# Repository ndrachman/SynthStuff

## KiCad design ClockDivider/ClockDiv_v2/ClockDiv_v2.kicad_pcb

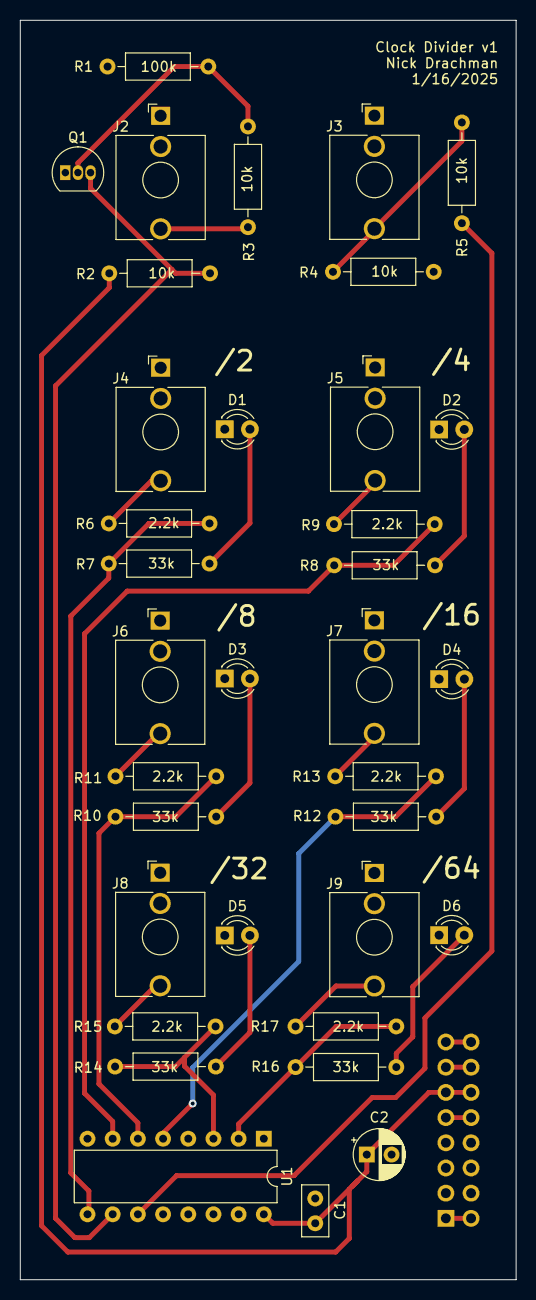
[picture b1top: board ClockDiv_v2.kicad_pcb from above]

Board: 2 copper layers, 50.0 x 127.0 mm, 36 parts (1 on the bottom side), 27 nets.

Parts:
C1: 0.1u; C_Disc_D5.0mm_W2.5mm_P2.50mm
C2: 10u; CP_Radial_D5.0mm_P2.50mm
D1, D2, D3, D4, D5, D6: LED; LED_D3.0mm
J2: ClockIn; Jack_3.5mm_QingPu_WQP-PJ398SM_Vertical_CircularHoles
J3: ResetIn; Jack_3.5mm_QingPu_WQP-PJ398SM_Vertical_CircularHoles
J4: /2; Jack_3.5mm_QingPu_WQP-PJ398SM_Vertical_CircularHoles
J5: /4; Jack_3.5mm_QingPu_WQP-PJ398SM_Vertical_CircularHoles
J6: /8; Jack_3.5mm_QingPu_WQP-PJ398SM_Vertical_CircularHoles
J7: /16; Jack_3.5mm_QingPu_WQP-PJ398SM_Vertical_CircularHoles
J8: /32; Jack_3.5mm_QingPu_WQP-PJ398SM_Vertical_CircularHoles
J9: /64; Jack_3.5mm_QingPu_WQP-PJ398SM_Vertical_CircularHoles
J10: Conn_02x08_Odd_Even; PinHeader_2x08_P2.54mm_Vertical
Q1: 2N3904; TO-92_Inline
R1: 100k; R_Axial_DIN0207_L6.3mm_D2.5mm_P10.16mm_Horizontal
R2, R3, R4, R5: 10k; R_Axial_DIN0207_L6.3mm_D2.5mm_P10.16mm_Horizontal
R6: 2.2k; R_Axial_DIN0207_L6.3mm_D2.5mm_P10.16mm_Horizontal
R7, R8, R10, R12, R14, R16: 33k; R_Axial_DIN0207_L6.3mm_D2.5mm_P10.16mm_Horizontal
R9, R11, R13, R15, R17: 2k2; R_Axial_DIN0207_L6.3mm_D2.5mm_P10.16mm_Horizontal
U1: 4040; DIP-16_W7.62mm

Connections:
+5V: C1.1, C2.1, J10.11, J10.12, R2.1, U1.16 (VDD)
+12V: J10.9, J10.10
-12V: J10.1, J10.2
GND: C1.2, C2.2, D1.1 (K), D2.1 (K), D3.1 (K), D4.1 (K), D5.1 (K), D6.1 (K), J2.S, J3.S, J4.S, J5.S, J6.S, J7.S, J8.S, J9.S, J10.3, J10.4, J10.5, J10.6, J10.7, J10.8, Q1.1 (E), R1.1, R4.2, U1.8 (VSS)
unnamed: D1.2 (A), R7.2
unnamed: D2.2 (A), R8.2
unnamed: D3.2 (A), R10.2
unnamed: D4.2 (A), R12.2
unnamed: D5.2 (A), R14.2
unnamed: D6.2 (A), R16.2
unnamed: J2.T, R3.2
unnamed: J3.T, R4.1, R5.2
unnamed: J4.T, R6.1
unnamed: J5.T, R9.1
unnamed: J6.T, R11.1
unnamed: J7.T, R13.1
unnamed: J8.T, R15.1
unnamed: J9.T, R17.1
unnamed: Q1.2 (B), R1.2, R3.1
unnamed: Q1.3 (C), R2.2, U1.10 (CLK)
unnamed: R6.2, R7.1, U1.9 (Q0)
unnamed: R8.1, R9.2, U1.7 (Q1)
unnamed: R10.1, R11.2, U1.6 (Q2)
unnamed: R12.1, R13.2, U1.5 (Q3)
unnamed: R14.1, R15.2, U1.3 (Q4)
unnamed: R16.1, R17.2, U1.2 (Q5)
unnamed: R5.1, U1.11 (Reset)

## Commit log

2025-01-10 Initial commit - adding ClockDiv_v2 files
2025-01-16 Redesigned PCB
2025-01-21 version submitted to JLBPCB
